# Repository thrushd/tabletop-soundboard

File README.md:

# Tabletop Soundboard
## In progress!
A simple, compact, easy to use device to add music, ambiance, and sound effects to any tabletop RPG.

## How To
All data is given to the device through a micro SD card. Audio files, the config, and gif are all placed in the root directory with no sub folders.

### Listening
There are two audio outputs on the device, USB audio and a standard 3.5mm jack. For the USB audio, you can easily loop it back to play through your computer speakers, a connected bluetooth speaker, etc. Instructions for setting up this loopback can be found [here](https://www.addictivetips.com/windows-tips/output-mic-sound-to-speakers-windows-10/) for windows. 

### Scenes and Settings
Sounds are organized into 'scenes', with each scene containing up to 8 tracks (sound files). This organization is set with a configuration file, written in [TOML](https://toml.io/en/). There are three main settings, which can be set at three different levels: global, scene, and track level. Priority for settings is always given to lower levels, so a track level setting will always override a scene level setting, etc. If a setting is not given to a scene or track it will use the next highest defined setting.

| Setting | Description |
| --- | --- |
| `gain` | The volume level, decimal values from `0-1` |
| `loop` | Whether a track should start playing again when it reaches the end, `true` or `false` |
| `play` | Whether a track should start playing immediately when a scene is activated, `true` or `false` |
| `name` | Override the name of the scene or track filename, used in scene and track definitions |
| `filename` | Filename of sound, used in track definitions, include the extension |
| `tracks` | A list of filenames used to create a scene with minimal input, same conventions as `filename` |

A scene is defined by making a name after the keyword `scenes`, enclosed in brackets. So to make a new scene called `tavern` you would write: `[scenes.tavern]`. Under this definition you can add your scene level settings. After that you can define tracks. This follows the same convention, just the scene name followed by a number representing which track it should be. So to define track 3 in scene `tavern` you would write: `[tavern.3]`. Same as the scene level definitions, under this you put all of your track level settings.

### Fixed Tracks
Sometimes you might have a sound that is used in every scene. So instead of copy-pasting the definition of the track into each scene, you can define it as a special `fixed` track with the notation `[fixed.N]`, with `N` being the track number. This does however mean you cannot have a scene named `fixed`.

### Startup Animation
Gifs are fun, so when the device is powered on it will play a gif on the main display if one is present on the SD card. This name can be changed in the config file under the table `[gifs]` with the setting `startup`. If this behaviour is not desired it can be left out of the config and the device will boot without it.

### Config Example
```TOML
# Default Settings, required
[default]
gain = 0.5
loop = false
play = false

# Startup animation filename
[gifs]
startup = "startup.gif"

# Create fixed tracks that don't change depending on which scene you are in
# If track.n is declared in a scene it is ignored and overriden with the below items
[fixed.7]
filename = "dj_airhorn.wav"
name = "Nat 20"
gain = 1.0
[fixed.8]
filename = "sad_trombone.wav"
name = "Nat 1"
gain = 1.0

# Create a scene
[scenes.tavern]
name = "Old Ivey Tavern"  # rename the scene if desired, otherwise it will show as 'tavern'
[tavern.1]  # add a track
filename = "tavern_sounds_1.wav"  # specify the filename
name = "Tavern Sounds"  # change the displayed name if you want
play = true  # set if it should play on scene start
loop = true  # set if the track should loop or not
gain = 0.3  # set a non default volume gain
[tavern.2]  # add another track
filename = "piano_3.wav"
name = "Piano"
play = true
gain = 0.75
[tavern.3]  # this track is fine with all of the default settings, no need to override
filename = "bang.wav"

[scenes.camp]
gain = 1.0
[camp.1]
filename = "wolf_howl.wav"
[camp.2]
filename = "wind.wav"
gain = 0.2
loop = true
play = true
[camp.3]
filename = "crackling_campfire.wav"
gain = 0.75
loop = true
play = true

# If defalt settings are fine it can get very minimal, just a list of the file names
[scenes.mountain]
loop = true
tracks = ["mountain_ambiance.wav", "avalanch.wav", "yetti_growl.wav"]
```

## Audio Files
### Format
The audio is handled by the teensy audio library, which only supports a certain format (16 bit PCM, 44100 Hz WAV files). Since most online resources provide all kinds of formats a simple tool is provided to convert these to the proper WAV format. It can be found under `/audio-convert`.

### Editing
[Audacity](https://www.audacityteam.org/) is a great free, open source, cross platform audio editor. It can be used to trim tracks you find online, add fade in/out, and other effects. 

[Getting started](https://manual.audacityteam.org/quick_help.html)

### Sources
- [Tabletop Audio](https://tabletopaudio.com/) - Good for longer, ambient tracks
- [Battlebards](https://battlebards.com/#/tracks) - Tons of variety, music, soundscapes, effects, voiceovers, but it is paid
- [Ambient Mixer RPG Category](https://rpg.ambient-mixer.com/) - Ambiance, user curated collections of tracks, no easy download, but there are sources given for most tracks
- [Freesound](https://freesound.org/) - Free, huge variety, need an account to download
- [SoundBible](https://soundbible.com/) - Free, decent collection, WAV format (need to right click and `save link as...` to actually download)
- [mixkit](https://mixkit.co/free-sound-effects/) - Free, decent collection, WAV format
- [pixabay](https://pixabay.com/sound-effects/) - Free, music and sound effects

## Feature Wishlist
- Scrolling text for longer file and scene names

## History
| Date | Firmware | PCBA | Case | 
| ---- | -------- | ---- | ---- |
| 2022-02-19 | MVP working on breadboard | | |
| 2022-03-29 |  | First prototypes ordered | First prototypes ordered |
| 2023-04-22 | Ported to PCBA | Assembled and working | |

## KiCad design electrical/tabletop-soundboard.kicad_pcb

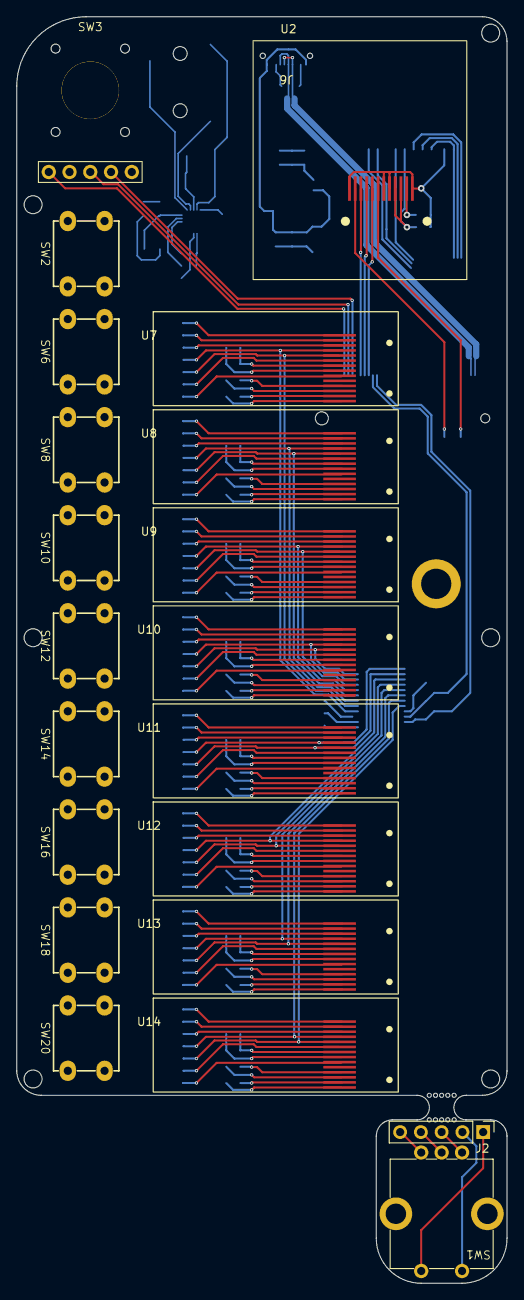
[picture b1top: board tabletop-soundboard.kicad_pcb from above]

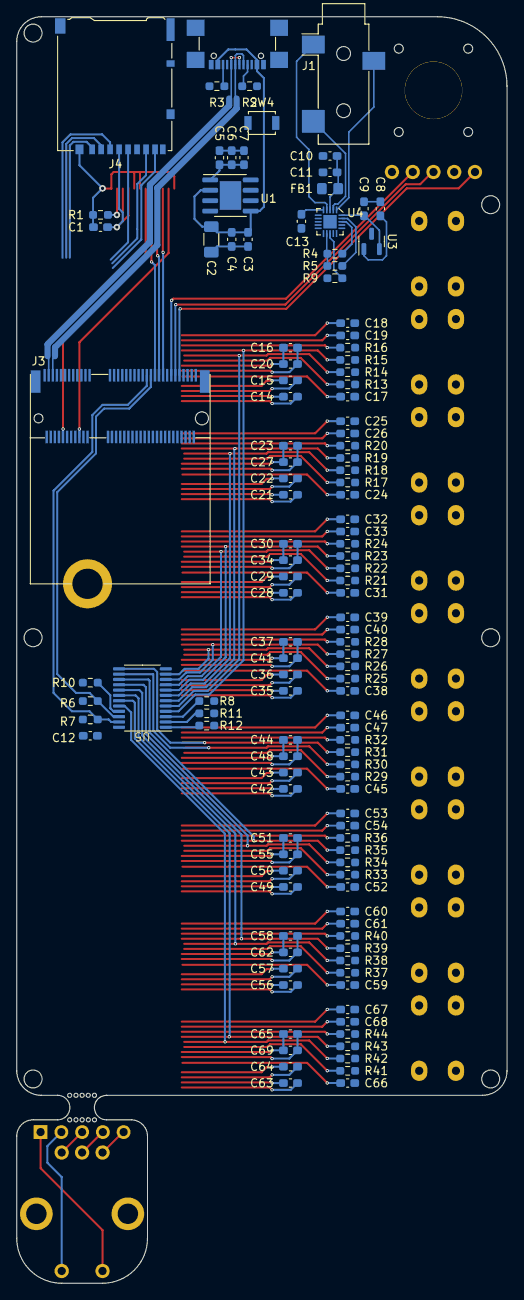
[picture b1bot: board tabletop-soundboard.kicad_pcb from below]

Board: 2 copper layers, 60.0 x 155.0 mm, 147 parts (125 on the bottom side), 145 nets.

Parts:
C1, C5, C8, C9: 1uF; C_0603_1608Metric_Pad1.08x0.95mm_HandSolder
C2: 10uF; C_1206_3216Metric_Pad1.33x1.80mm_HandSolder
C3, C6: 0.22uF; C_0603_1608Metric_Pad1.08x0.95mm_HandSolder
C4, C7, C11: 0.1uF; C_0603_1608Metric_Pad1.08x0.95mm_HandSolder
C10: 2.2uF; C_0603_1608Metric_Pad1.08x0.95mm_HandSolder
C12: 10uF; C_0603_1608Metric_Pad1.08x0.95mm_HandSolder
C13: 0.15uF; C_0603_1608Metric_Pad1.08x0.95mm_HandSolder
C14, C15, C16, C20, C21, C22, C23, C27, C28, C29, C30, C34, C35, C36, C37, C41, C42, C43, C44, C48, C49, C50, C51, C55, C56, C57, C58, C62, C63, C64, C65, C69: 1uf; C_0603_1608Metric_Pad1.08x0.95mm_HandSolder
C17, C24, C31, C38, C45, C52, C59, C66: 22nf; C_0603_1608Metric_Pad1.08x0.95mm_HandSolder
C18, C25, C32, C39, C46, C53, C60, C67: 2.2uf; C_0603_1608Metric_Pad1.08x0.95mm_HandSolder
C19, C26, C33, C40, C47, C54, C61, C68: 4.7uf; C_0603_1608Metric_Pad1.08x0.95mm_HandSolder
FB1: Ferrite 600; R_0805_2012Metric_Pad1.20x1.40mm_HandSolder
J1: AudioJack3; Jack_3.5mm_CUI_SJ-3523-SMT_Horizontal
J2: HEADER; PinHeader_1x05_P2.54mm_Vertical
J3: micromod_teensy; M.2_connector_TE-2199230-4
J4: Micro_SD_Card_Det2; microSD_HC_Hirose_DM3AT-SF-PEJM5
J5: standoff_9774025151R
J6: USB_C_Receptacle; USB_C_Receptacle_GCT_USB4110
R1: 10; R_0603_1608Metric_Pad0.98x0.95mm_HandSolder
R2, R3: 5.1k; R_0603_1608Metric_Pad0.98x0.95mm_HandSolder
R4, R5: 2.2k; R_0603_1608Metric_Pad0.98x0.95mm_HandSolder
R6, R7, R8, R10, R11, R12: 10k; R_0603_1608Metric_Pad0.98x0.95mm_HandSolder
R9: 100; R_0603_1608Metric_Pad0.98x0.95mm_HandSolder
R13, R14, R15, R17, R18, R19, R21, R22, R23, R25, R26, R27, R29, R30, R31, R33, R34, R35, R37, R38, R39, R41, R42, R43: 4.7k; R_0603_1608Metric_Pad0.98x0.95mm_HandSolder
R16, R20, R24, R28, R32, R36, R40, R44: 390K; R_0603_1608Metric_Pad0.98x0.95mm_HandSolder
SW1: ENCODER; encoder_PEC12R-4215F-S0024
SW2: STOP ALL; BUTTON_SOFT_TACTILE
SW3: UNDER MOUNTED ENCODER; encoder_PEC12R-4XXXF-SXXX_undermount
SW4: PROG; SW_SPST_B3U-1000P
SW6, SW8, SW10, SW12, SW14, SW16, SW18, SW20: TRIGGER; BUTTON_SOFT_TACTILE
U1: AP7361C-33SP; SOIC-8
U2: ER-TFT013-2
U3: AP7313-12SRG-7; SOT-23
U4: SGTL5000XNLA3; QFN-20-1EP_3x3mm_P0.4mm_EP1.65x1.65mm
U5: TCA9548APWR; TSSOP-24-0.65mm
U6: MICROMOD
U7, U8, U9, U10, U11, U12, U13, U14: ER-OLED0.91-7W; ER-OLED0.91-1
mouse-bite-3mm-slot: mouse-bite-3mm-slot

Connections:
+3.3V: C1.1, C5.1, C6.1, C7.1, C8.1, C12.1, C16.1, C20.2, C23.1, C27.2, C30.1, C34.2, C37.1, C41.2, C44.1, C48.2, C51.1, C55.2, C58.1, C62.2, C65.1, C69.2, FB1.1, J3.2 (3.3V), J3.74 (3.3V), J4.4 (VDD), R4.2, R5.2, R6.2, R7.2, R8.2, R13.1, R14.1, R15.1, R17.1, R18.1, R19.1, R21.1, R22.1, R23.1, R25.1, R26.1, R27.1, R29.1, R30.1, R31.1, R33.1, R34.1, R35.1, R37.1, R38.1, R39.1, R41.1, R42.1, R43.1, U1.1 (OUT), U2.3 (LEDA), U2.4 (VDD), U3.1 (IN), U4.12 (VDDIO), U5.24 (VCC), U7.5 (VBAT), U7.8 (VDD), U8.5 (VBAT), U8.8 (VDD), U9.5 (VBAT), U9.8 (VDD), U10.5 (VBAT), U10.8 (VDD), U11.5 (VBAT), U11.8 (VDD), U12.5 (VBAT), U12.8 (VDD), U13.5 (VBAT), U13.8 (VDD), U14.5 (VBAT), U14.8 (VDD)
/module1/SCL: R18.2, U5.7 (SC1), U8.10 (SCL)
/module1/SDA: R19.2, U5.6 (SD1), U8.11 (SDA)
/module2/SCL: R22.2, U5.9 (SC2), U9.10 (SCL)
/module2/SDA: R23.2, U5.8 (SD2), U9.11 (SDA)
/module3/SCL: R26.2, U5.11 (SC3), U10.10 (SCL)
/module3/SDA: R27.2, U5.10 (SD3), U10.11 (SDA)
/module4/SCL: R30.2, U5.14 (SC4), U11.10 (SCL)
/module4/SDA: R31.2, U5.13 (SD4), U11.11 (SDA)
/module5/SCL: R34.2, U5.16 (SC5), U12.10 (SCL)
/module5/SDA: R35.2, U5.15 (SD5), U12.11 (SDA)
/module6/SCL: R38.2, U5.18 (SC6), U13.10 (SCL)
/module6/SDA: R39.2, U5.17 (SD6), U13.11 (SDA)
/module7/SCL: R42.2, U5.20 (SC7), U14.10 (SCL)
/module7/SDA: R43.2, U5.19 (SD7), U14.11 (SDA)
/module/SCL: R14.2, U5.5 (SC0), U7.10 (SCL)
/module/SDA: R15.2, U5.4 (SD0), U7.11 (SDA)
AUD_BCLK: J3.50 (AUD_BCLK/21), U4.15 (I2S_SCLK)
AUD_IN: J3.54 (AUD_IN/8), U4.16 (I2S_DOUT)
AUD_LRCLK: J3.52 (AUD_LRCLK/20), U4.14 (I2S_LRCLK)
AUD_MCLK: J3.58 (AUD_MCLK/23), R9.1
AUD_OUT: J3.56 (AUD_OUT/7), U4.17 (I2S_DIN)
D0: J3.10 (D0/4), U2.7 (D/C)
D1: J3.18 (D1/5), U2.11 (RESET)
G0: J3.40 (G0/40), SW6.1, SW6.2
G1: J3.42 (G1/41), SW8.1, SW8.2
G2: J3.44 (G2/42), SW10.1, SW10.2
G3: J3.46 (G3/43), SW12.1, SW12.2
G4: J3.48 (G4/44), SW14.1, SW14.2
G5: J3.73 (G5/45), SW16.1, SW16.2
G6: J3.71 (G6/6), SW18.1, SW18.2
G7: J3.69 (G7/9), SW20.1, SW20.2
G8: J3.67 (G8/26), SW3.1 (S1)
G9: J3.65 (G9/32), SW3.A
G10: J3.63 (G10/33), SW3.B
G11: J3.8 (G11/27), SW2.1, SW2.2
GND: C1.2, C2.2, C3.2, C4.2, C5.2, C6.2, C7.2, C8.2, C9.2, C10.2, C11.2, C12.2, C13.2, C16.2, C17.2, C18.2, C19.2, C20.1, C23.2, C24.2, C25.2, C26.2, C27.1, C30.2, C31.2, C32.2, C33.2, C34.1, C37.2, C38.2, C39.2, C40.2, C41.1, C44.2, C45.2, C46.2, C47.2, C48.1, C51.2, C52.2, C53.2, C54.2, C55.1, C58.2, C59.2, C60.2, C61.2, C62.1, C65.2, C66.2, C67.2, C68.2, C69.1, J3.1 (GND), J3.7 (GND), J3.33 (GND), J3.36 (GND), J3.39 (GND), J3.45 (GND), J3.75 (GND), J4.6 (VSS), J4.11 (SHIELD), J5.1, J6.A1 (GND), J6.A12 (GND), J6.B1 (GND), J6.B12 (GND), R1.1, R2.2, R3.2, R10.1, R11.1, R12.1, R16.2, R20.2, R24.2, R28.2, R32.2, R36.2, R40.2, R44.2, SW2.3, SW2.4, SW3.2 (S2), SW3.C, SW4.1, SW6.3, SW6.4, SW8.3, SW8.4, SW10.3, SW10.4, SW12.3, SW12.4, SW14.3, SW14.4, SW16.3, SW16.4, SW18.3, SW18.4, SW20.3, SW20.4, U1.4 (GND), U2.1 (GND), U2.5 (GND), U2.6 (GND), U2.12 (GND), U3.3 (GND), U4.21 (GND), U5.12 (GND), U7.7 (VSS), U8.7 (VSS), U9.7 (VSS), U10.7 (VSS), U11.7 (VSS), U12.7 (VSS), U13.7 (VSS), U14.7 (VSS)
I2C_SCL: J3.14 (I2C_SCL/19), R5.1, U4.19 (CTRL_CLK)
I2C_SCL_1: J3.53 (I2C_SCL1/24), R6.1, U5.22 (SCL)
I2C_SDA: J3.12 (I2C_SDA/18), R4.1, U4.18 (CTRL_DATA)
I2C_SDA_1: J3.51 (I2C_SDA1/25), R7.1, U5.23 (SDA)
unnamed: J2.1, SW1.2 (S2)
unnamed: J2.2, SW1.1 (S1)
unnamed: J2.3, SW1.A
unnamed: J2.4, SW1.C
unnamed: J2.5, SW1.B
unnamed: J3.11 (BOOT/PROG), SW4.2
unnamed: J3.62 (SDIO_CMD/37), J4.3 (CMD)
unnamed: J3.64 (SDIO_DATA0/35), J4.7 (DAT0)
unnamed: J3.66 (SDIO_DATA1/34), J4.8 (DAT1)
unnamed: J3.68 (SDIO_DATA2/39), J4.1 (DAT2)
unnamed: J3.70 (SDIO_DATA3/38), J4.2 (DAT3/CD)
unnamed: J3.60 (SDIO_SCK/36), J4.5 (CLK)
unnamed: J6.A5 (CC1), R2.1
unnamed: J6.B5 (CC2), R3.1
unnamed: R1.2, U2.2 (LEDK)
unnamed: C9.1, U3.2 (OUT), U4.20 (VDDD)
unnamed: J1.S, U4.4 (HP_L)
unnamed: J1.R, U4.1 (HP_R)
unnamed: J1.T, U4.2 (HP_VGND)
unnamed: R9.2, U4.13 (SYS_MCLK)
unnamed: C13.1, U4.5 (VAG)
unnamed: C10.1, C11.1, FB1.2, U4.3 (VDDA)
unnamed: R12.2, U5.1 (A0)
unnamed: R11.2, U5.2 (A1)
unnamed: R10.2, U5.21 (A2)
unnamed: R8.1, U5.3 (~RESET)
unnamed: C15.2, U7.4 (C1N)
unnamed: C15.1, U7.3 (C1P)
unnamed: C14.2, U7.2 (C2N)
unnamed: C14.1, U7.1 (C2P)
unnamed: R16.1, U7.12 (IREF)
unnamed: R13.2, U7.9 (RES)
unnamed: C17.1, U7.6 (VBREF)
unnamed: C18.1, U7.14 (VCC)
unnamed: C19.1, U7.13 (VCOMH)
unnamed: C22.2, U8.4 (C1N)
unnamed: C22.1, U8.3 (C1P)
unnamed: C21.2, U8.2 (C2N)
unnamed: C21.1, U8.1 (C2P)
unnamed: R20.1, U8.12 (IREF)
unnamed: R17.2, U8.9 (RES)
unnamed: C24.1, U8.6 (VBREF)
unnamed: C25.1, U8.14 (VCC)
unnamed: C26.1, U8.13 (VCOMH)
unnamed: C29.2, U9.4 (C1N)
unnamed: C29.1, U9.3 (C1P)
unnamed: C28.2, U9.2 (C2N)
unnamed: C28.1, U9.1 (C2P)
unnamed: R24.1, U9.12 (IREF)
unnamed: R21.2, U9.9 (RES)
unnamed: C31.1, U9.6 (VBREF)
unnamed: C32.1, U9.14 (VCC)
unnamed: C33.1, U9.13 (VCOMH)
unnamed: C36.2, U10.4 (C1N)
unnamed: C36.1, U10.3 (C1P)
unnamed: C35.2, U10.2 (C2N)
unnamed: C35.1, U10.1 (C2P)
unnamed: R28.1, U10.12 (IREF)
unnamed: R25.2, U10.9 (RES)
unnamed: C38.1, U10.6 (VBREF)
unnamed: C39.1, U10.14 (VCC)
unnamed: C40.1, U10.13 (VCOMH)
unnamed: C43.2, U11.4 (C1N)
unnamed: C43.1, U11.3 (C1P)
unnamed: C42.2, U11.2 (C2N)
unnamed: C42.1, U11.1 (C2P)
unnamed: R32.1, U11.12 (IREF)
unnamed: R29.2, U11.9 (RES)
unnamed: C45.1, U11.6 (VBREF)
unnamed: C46.1, U11.14 (VCC)
unnamed: C47.1, U11.13 (VCOMH)
unnamed: C50.2, U12.4 (C1N)
unnamed: C50.1, U12.3 (C1P)
unnamed: C49.2, U12.2 (C2N)
unnamed: C49.1, U12.1 (C2P)
unnamed: R36.1, U12.12 (IREF)
unnamed: R33.2, U12.9 (RES)
unnamed: C52.1, U12.6 (VBREF)
unnamed: C53.1, U12.14 (VCC)
unnamed: C54.1, U12.13 (VCOMH)
unnamed: C57.2, U13.4 (C1N)
unnamed: C57.1, U13.3 (C1P)
unnamed: C56.2, U13.2 (C2N)
unnamed: C56.1, U13.1 (C2P)
unnamed: R40.1, U13.12 (IREF)
unnamed: R37.2, U13.9 (RES)
unnamed: C59.1, U13.6 (VBREF)
unnamed: C60.1, U13.14 (VCC)
unnamed: C61.1, U13.13 (VCOMH)
unnamed: C64.2, U14.4 (C1N)
unnamed: C64.1, U14.3 (C1P)
unnamed: C63.2, U14.2 (C2N)
unnamed: C63.1, U14.1 (C2P)
unnamed: R44.1, U14.12 (IREF)
unnamed: R41.2, U14.9 (RES)
unnamed: C66.1, U14.6 (VBREF)
unnamed: C67.1, U14.14 (VCC)
unnamed: C68.1, U14.13 (VCOMH)
SPI_CLK: J3.57 (SPI_SCK/13), U2.9 (SCL)
SPI_COPI: J3.59 (SPI_COPI/11), U2.10 (SDA)
SPI_CS: J3.55 (SPI_CS/10), U2.8 (CS)
USB_N: J3.5 (USB_D-), J6.A7 (D-), J6.B7 (D-)
USB_P: J3.3 (USB_D+), J6.A6 (D+), J6.B6 (D+)
VCC: C2.1, C3.1, C4.1, J3.9 (USB_VIN/V_USB), J6.A4 (VBUS), J6.A9 (VBUS), J6.B4 (VBUS), J6.B9 (VBUS), U1.2 (EN), U1.5 (IN)

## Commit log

2022-12-25 Added initial files
    First commit, config file loading is working
2022-12-25 broke read_config functions into their own files
2022-12-25 Started display integration, d20 startup animation working
2022-12-27 Basic prototype of main screen scene selection
2023-01-02 Started on a module class, not fully working yet
2023-01-03 Added mostly complete module display
2023-01-07 Added gain adjustment
2023-01-16 added soundboard class and am reworking read_config
2023-01-16 Added soundboard class and am working on reworking read_config. Also added a gif display class that is not working
2023-01-17 Removed gif player class, now works as classless module
2023-01-18 Read config is almost working, just doesn't seem to actually be modifying the values outside the functions
2023-01-31 I need to show dan some stuff
2023-02-01 Code has seen the light of Dan
2023-02-01 Dan betrayed me
2023-02-02 Moving load config into the soundboard for testing
2023-02-06 Read config is working again! stupid fixed tracks >.<
2023-02-11 Nuked soundboard as a class, main4lyfebb
2023-02-14 Changes for Lauren's expert eye to gaze upon
2023-02-15 Things are mostly all working together, with only a couple more bugs
2023-02-18 Things are working more than they were!
2023-02-20 MVP achieved!
2023-04-10 Added electrical and mechanical first revisions
2023-04-22 Started to port firmware to micromod / PCB layout
2023-04-23 Updated documentation and organized
2023-05-06 Added example sd card files, including audio
